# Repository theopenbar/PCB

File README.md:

# PCB-1
I2C Controller Board based on MCP23008
## This readme clearly shows how to use make the project step by step in simple ways happy making :)

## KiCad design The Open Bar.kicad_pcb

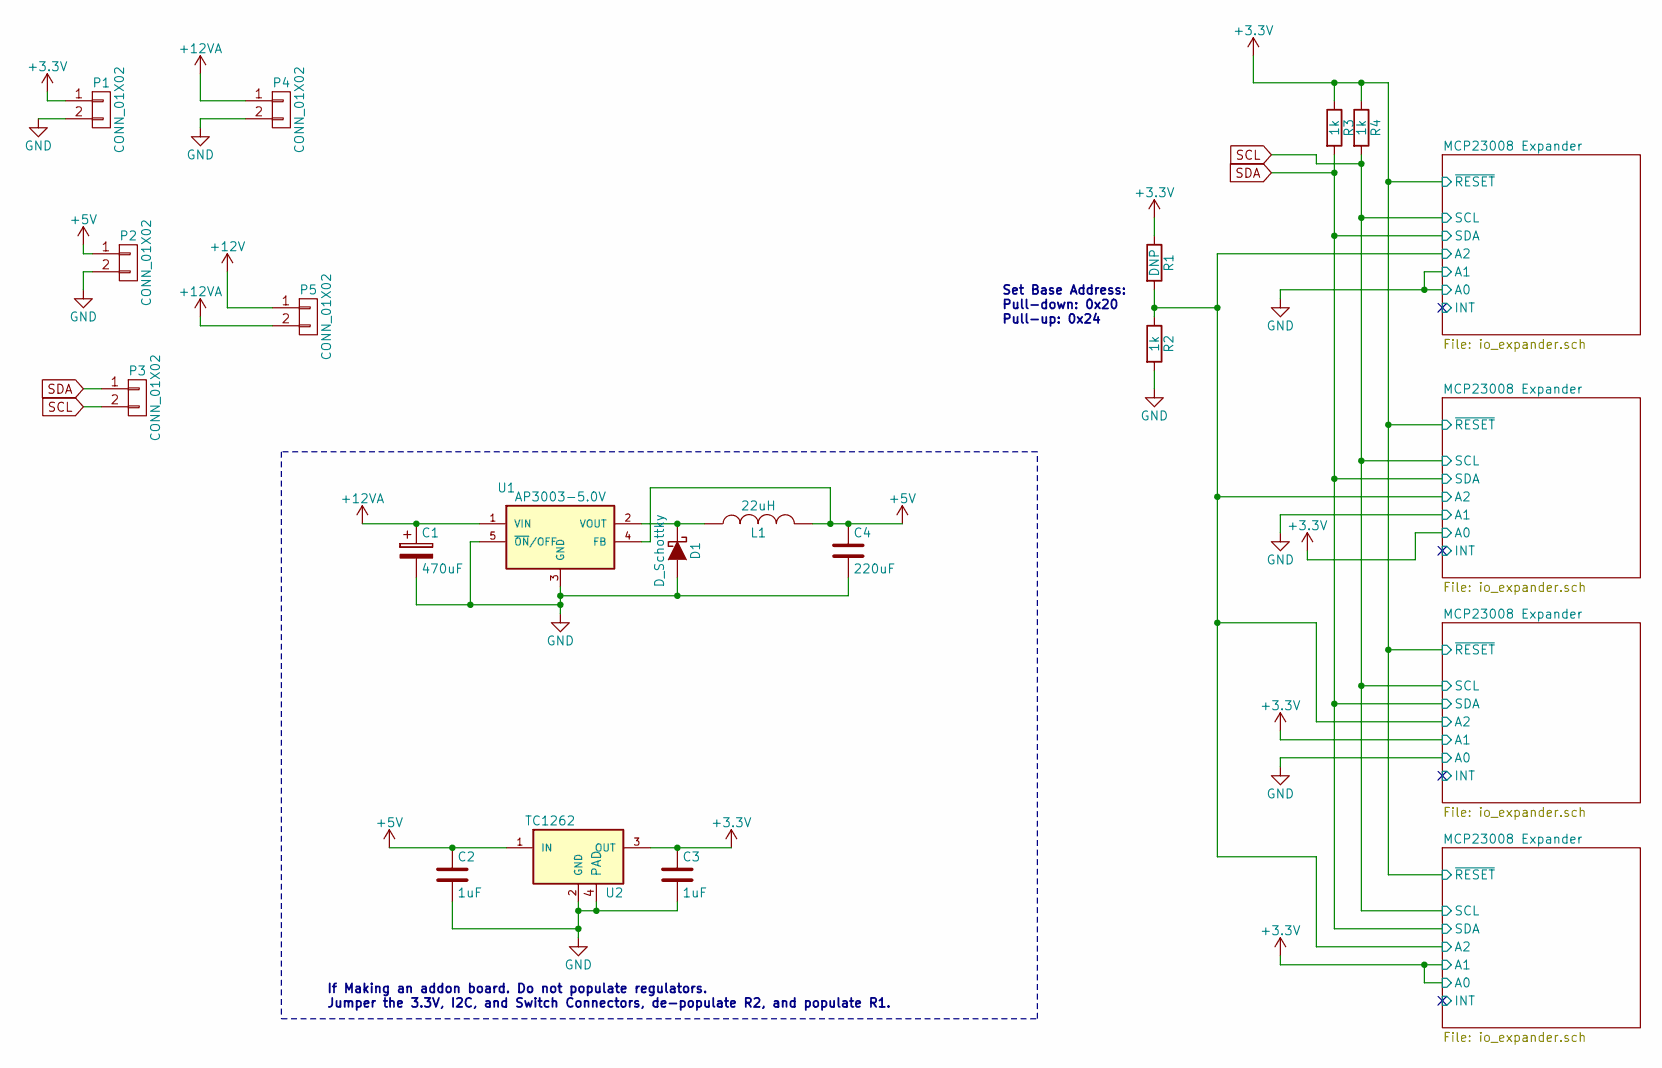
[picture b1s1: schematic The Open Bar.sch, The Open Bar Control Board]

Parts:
C1: 470uF; c_elec_10x10
C2, C3: 1uF; C_0402
C4: 220uF; C_1210
D1: D_Schottky; Diode_DO-201AD_Horizontal_RM15
L1: 22uH; SELF-WE-PD-XXL
P1, P2, P3, P4, P5: CONN_01X02; TerminalBlock_Pheonix_PT-3.5mm_2pol
R1: DNP; R_0402
R2, R3, R4: 1k; R_0402
U1: AP3003-5.0V; TO-263-5Lead
U2: TC1262; SOT-223

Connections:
+3V3: C3.1, P1.1, R1.1, R3.1, R4.1, U2.3 (OUT); also elsewhere on the board
+5V: C2.1, C4.1, L1.2, P2.1, U1.4 (FB), U2.1 (IN)
+12V: P5.1; also elsewhere on the board
+12VA: C1.1, P4.1, P5.2, U1.1 (VIN)
/MCP23008 Expander/A2: R1.2, R2.1; also elsewhere on the board
GND: C1.2, C2.2, C3.2, C4.2, D1.2 (A), P1.2, P2.2, P4.2, R2.2, U1.3 (GND), U1.5 (~ON~/OFF), U2.2 (GND), U2.4 (PAD); also elsewhere on the board
unnamed: D1.1 (K), L1.1, U1.2 (VOUT)
SCL: P3.2, R4.2; also elsewhere on the board
SDA: P3.1, R3.2; also elsewhere on the board

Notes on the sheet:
Set Base Address: Pull-down: 0x20 Pull-up: 0x24
If Making an addon board. Do not populate regulators. Jumper the 3.3V, I2C, and Switch Connectors, de-populate R2, and populate R1.

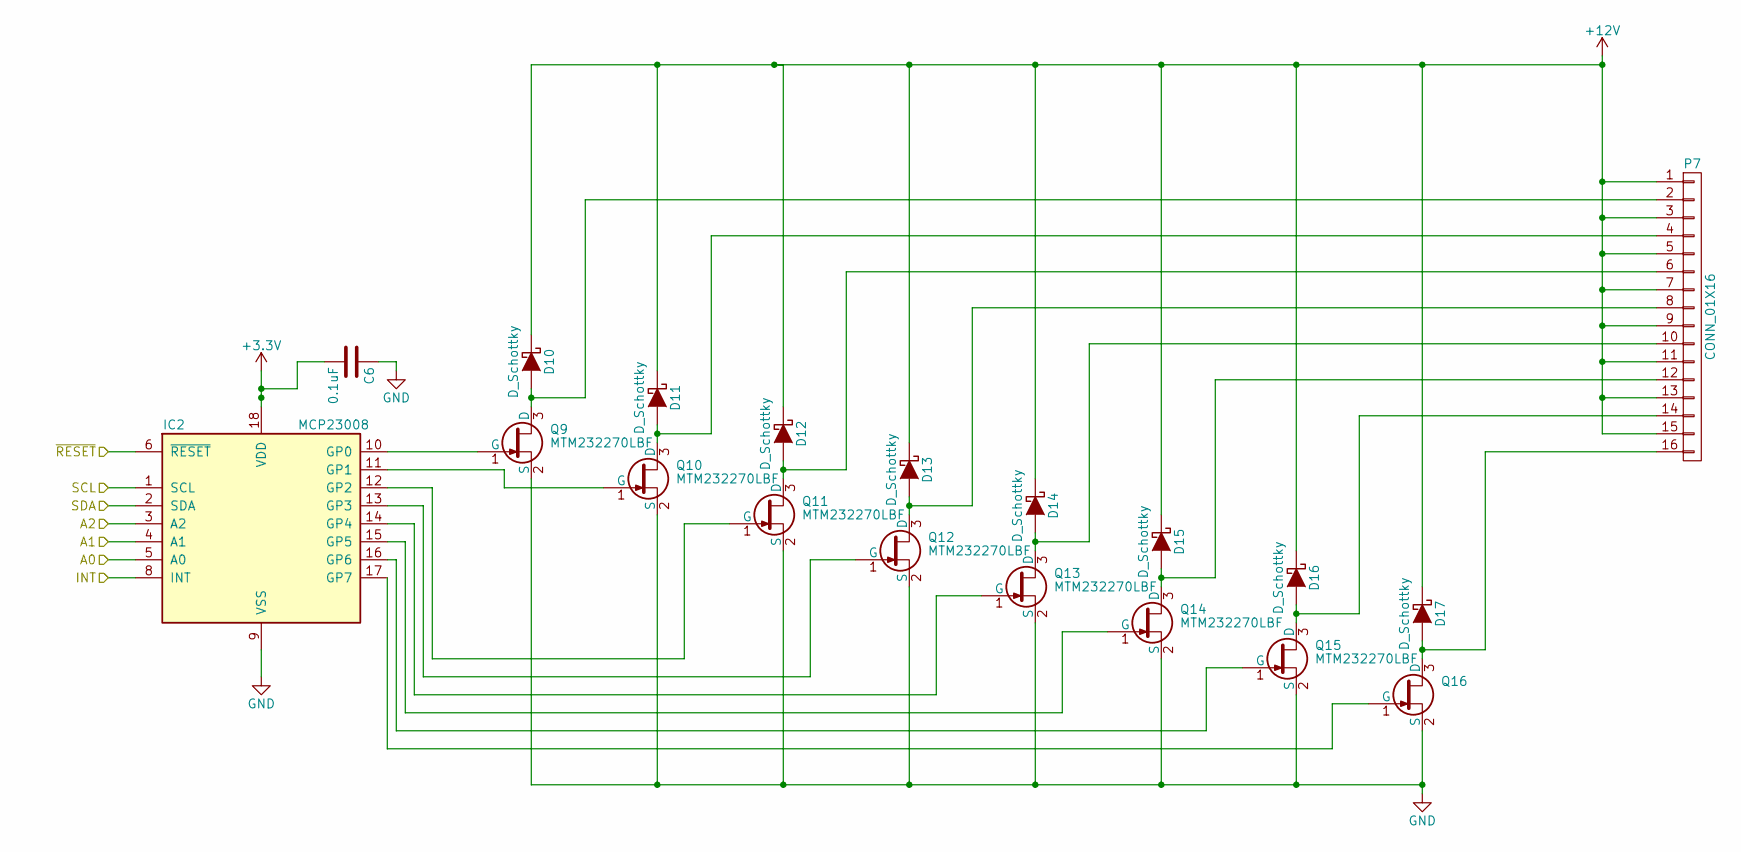
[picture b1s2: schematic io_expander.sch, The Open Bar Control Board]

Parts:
C5: 0.1uF; C_0402
D2, D3, D4, D5, D6, D7, D8, D17: D_Schottky; microSMP
IC1: MCP23008; SOIC-18_7.5x11.6mm_Pitch1.27mm
P6: CONN_01X16; TerminalBlock_Pheonix_PT-3.5mm_16pol
Q1, Q2, Q3, Q4, Q5, Q6, Q7, Q8: MTM232270LBF; SC-70

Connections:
+3V3: C5.2, IC1.6 (~RESET), IC1.18 (VDD); also elsewhere on the board
+12V: D2.1 (K), D3.1 (K), D4.1 (K), D5.1 (K), D6.1 (K), D7.1 (K), D8.1 (K), D17.1 (K), P6.1, P6.3, P6.5, P6.7, P6.9, P6.11, P6.13, P6.15; also elsewhere on the board
/MCP23008 Expander/A2: IC1.3 (A2); also elsewhere on the board
/MCP23008 Expander/INT: IC1.8 (INT); also elsewhere on the board
GND: C5.1, IC1.4 (A1), IC1.5 (A0), IC1.9 (VSS), Q1.2 (S), Q2.2 (S), Q3.2 (S), Q4.2 (S), Q5.2 (S), Q6.2 (S), Q7.2 (S), Q8.2 (S); also elsewhere on the board
unnamed: D2.2 (A), P6.2, Q1.3 (D)
unnamed: D3.2 (A), P6.4, Q2.3 (D)
unnamed: D4.2 (A), P6.6, Q3.3 (D)
unnamed: D5.2 (A), P6.8, Q4.3 (D)
unnamed: D6.2 (A), P6.10, Q5.3 (D)
unnamed: D7.2 (A), P6.12, Q6.3 (D)
unnamed: D8.2 (A), P6.14, Q7.3 (D)
unnamed: IC1.10 (GP0), Q1.1 (G)
unnamed: IC1.11 (GP1), Q2.1 (G)
unnamed: IC1.12 (GP2), Q3.1 (G)
unnamed: IC1.13 (GP3), Q4.1 (G)
unnamed: IC1.14 (GP4), Q5.1 (G)
unnamed: IC1.15 (GP5), Q6.1 (G)
unnamed: IC1.16 (GP6), Q7.1 (G)
unnamed: IC1.17 (GP7), Q8.1 (G)
SCL: IC1.1 (SCL); also elsewhere on the board
SDA: IC1.2 (SDA); also elsewhere on the board

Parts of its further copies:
C6, C7, C8: 0.1uF; C_0402
D9, D10, D11, D12, D13, D14, D15, D16, D18, D19, D20, D21, D22, D23, D24, D25, D26, D27, D28, D29, D30, D31, D32, D33: D_Schottky; microSMP
IC2, IC3, IC4: MCP23008; SOIC-18_7.5x11.6mm_Pitch1.27mm
P7, P8, P9: CONN_01X16; TerminalBlock_Pheonix_PT-3.5mm_16pol
Q9, Q10, Q11, Q12, Q13, Q14, Q15, Q16, Q17, Q18, Q19, Q20, Q21, Q22, Q23, Q24, Q25, Q26, Q27, Q28, Q29, Q30, Q31, Q32: MTM232270LBF; SC-70

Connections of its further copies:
+3V3: C6.2, C7.2, C8.2, IC2.5 (A0), IC2.6 (~RESET), IC2.18 (VDD), IC3.4 (A1), IC3.6 (~RESET), IC3.18 (VDD), IC4.4 (A1), IC4.5 (A0), IC4.6 (~RESET), IC4.18 (VDD); also elsewhere on the board
+12V: D9.1 (K), D10.1 (K), D11.1 (K), D12.1 (K), D13.1 (K), D14.1 (K), D15.1 (K), D16.1 (K), D18.1 (K), D19.1 (K), D20.1 (K), D21.1 (K), D22.1 (K), D23.1 (K), D24.1 (K), D25.1 (K), D26.1 (K), D27.1 (K), D28.1 (K), D29.1 (K), D30.1 (K), D31.1 (K), D32.1 (K), D33.1 (K), P7.1, P7.3, P7.5, P7.7, P7.9, P7.11, P7.13, P7.15, P8.1, P8.3, P8.5, P8.7, P8.9, P8.11, P8.13, P8.15, P9.1, P9.3, P9.5, P9.7, P9.9, P9.11, P9.13, P9.15; also elsewhere on the board
/MCP23008 Expander/A2: IC2.3 (A2), IC3.3 (A2), IC4.3 (A2); also elsewhere on the board
/MCP23008 Expander/INT: IC2.8 (INT), IC3.8 (INT), IC4.8 (INT); also elsewhere on the board
GND: C6.1, C7.1, C8.1, IC2.4 (A1), IC2.9 (VSS), IC3.5 (A0), IC3.9 (VSS), IC4.9 (VSS), Q9.2 (S), Q10.2 (S), Q11.2 (S), Q12.2 (S), Q13.2 (S), Q14.2 (S), Q15.2 (S), Q16.2 (S), Q17.2 (S), Q18.2 (S), Q19.2 (S), Q20.2 (S), Q21.2 (S), Q22.2 (S), Q23.2 (S), Q24.2 (S), Q25.2 (S), Q26.2 (S), Q27.2 (S), Q28.2 (S), Q29.2 (S), Q30.2 (S), Q31.2 (S), Q32.2 (S); also elsewhere on the board
unnamed: D10.2 (A), P7.2, Q9.3 (D)
unnamed: D11.2 (A), P7.4, Q10.3 (D)
unnamed: D12.2 (A), P7.6, Q11.3 (D)
unnamed: D13.2 (A), P7.8, Q12.3 (D)
unnamed: D14.2 (A), P7.10, Q13.3 (D)
unnamed: D15.2 (A), P7.12, Q14.3 (D)
unnamed: D16.2 (A), P7.14, Q15.3 (D)
unnamed: D18.2 (A), P8.2, Q17.3 (D)
unnamed: D19.2 (A), P8.4, Q18.3 (D)
unnamed: D20.2 (A), P8.6, Q19.3 (D)
unnamed: D21.2 (A), P8.8, Q20.3 (D)
unnamed: D22.2 (A), P8.10, Q21.3 (D)
unnamed: D23.2 (A), P8.12, Q22.3 (D)
unnamed: D24.2 (A), P8.14, Q23.3 (D)
unnamed: D25.2 (A), P8.16, Q24.3 (D)
unnamed: D26.2 (A), P9.2, Q25.3 (D)
unnamed: D27.2 (A), P9.4, Q26.3 (D)
unnamed: D28.2 (A), P9.6, Q27.3 (D)
unnamed: D29.2 (A), P9.8, Q28.3 (D)
unnamed: D30.2 (A), P9.10, Q29.3 (D)
unnamed: D31.2 (A), P9.12, Q30.3 (D)
unnamed: D32.2 (A), P9.14, Q31.3 (D)
unnamed: D33.2 (A), P9.16, Q32.3 (D)
unnamed: IC2.10 (GP0), Q9.1 (G)
unnamed: IC2.11 (GP1), Q10.1 (G)
unnamed: IC2.12 (GP2), Q11.1 (G)
unnamed: IC2.13 (GP3), Q12.1 (G)
unnamed: IC2.14 (GP4), Q13.1 (G)
unnamed: IC2.15 (GP5), Q14.1 (G)
unnamed: IC2.16 (GP6), Q15.1 (G)
unnamed: IC2.17 (GP7), Q16.1 (G)
unnamed: IC3.10 (GP0), Q17.1 (G)
unnamed: IC3.11 (GP1), Q18.1 (G)
unnamed: IC3.12 (GP2), Q19.1 (G)
unnamed: IC3.13 (GP3), Q20.1 (G)
unnamed: IC3.14 (GP4), Q21.1 (G)
unnamed: IC3.15 (GP5), Q22.1 (G)
unnamed: IC3.16 (GP6), Q23.1 (G)
unnamed: IC3.17 (GP7), Q24.1 (G)
unnamed: IC4.10 (GP0), Q25.1 (G)
unnamed: IC4.11 (GP1), Q26.1 (G)
unnamed: IC4.12 (GP2), Q27.1 (G)
unnamed: IC4.13 (GP3), Q28.1 (G)
unnamed: IC4.14 (GP4), Q29.1 (G)
unnamed: IC4.15 (GP5), Q30.1 (G)
unnamed: IC4.16 (GP6), Q31.1 (G)
unnamed: IC4.17 (GP7), Q32.1 (G)
SCL: IC2.1 (SCL), IC3.1 (SCL), IC4.1 (SCL); also elsewhere on the board
SDA: IC2.2 (SDA), IC3.2 (SDA), IC4.2 (SDA); also elsewhere on the board

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
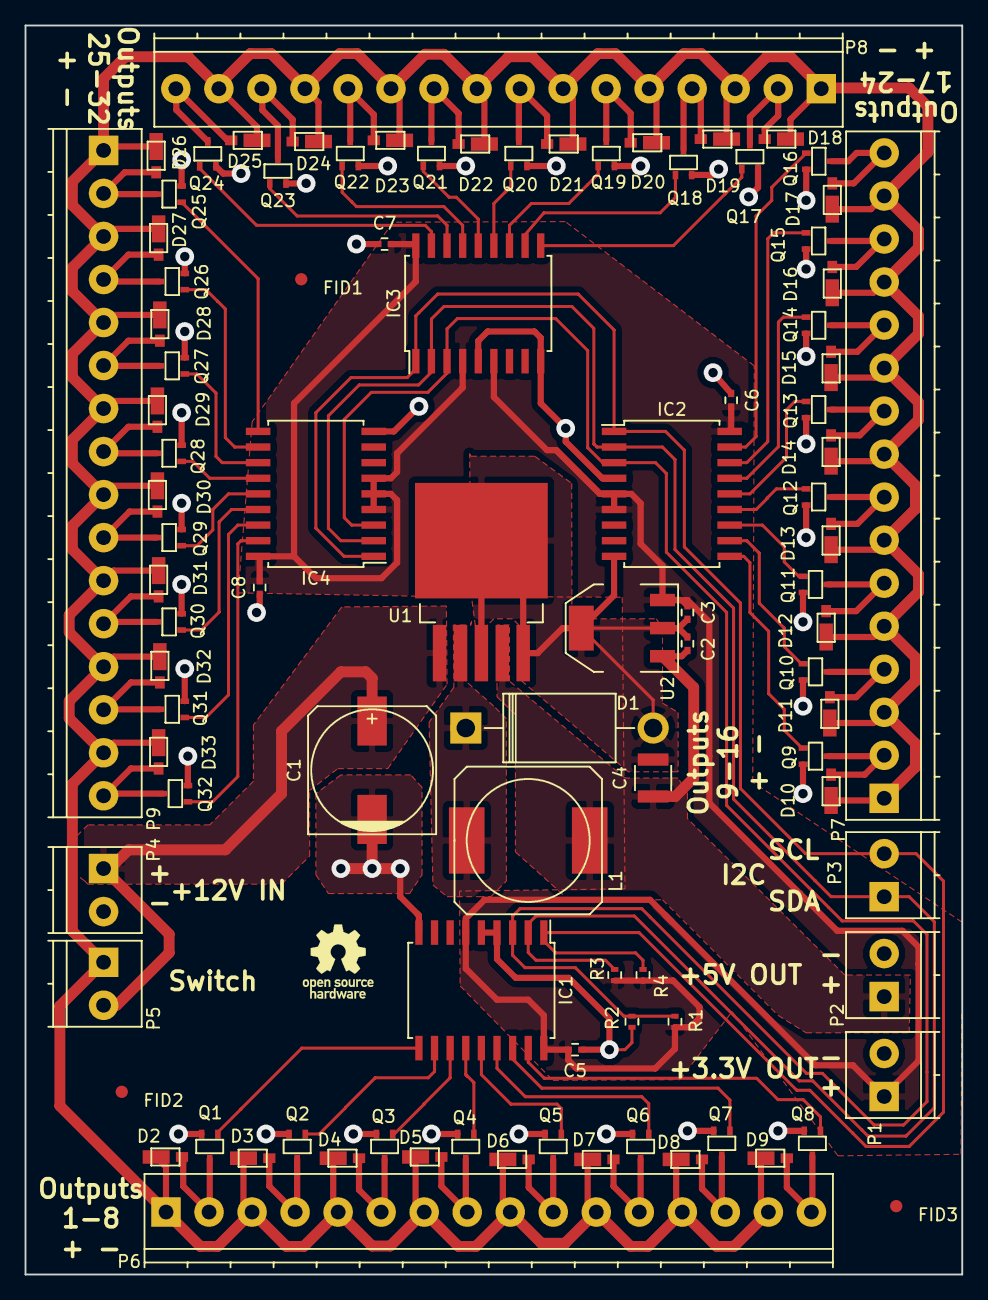
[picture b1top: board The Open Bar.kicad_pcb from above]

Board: 2 copper layers, 76.2 x 101.6 mm, 96 parts (0 on the bottom side), 74 nets.

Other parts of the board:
FID1, FID2, FID3: Fiducial_Modern_CopperTop; Fiducial_1mm_Dia_2.54mm_Outer_CopperTop

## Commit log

2016-08-04 Initial Commit Rev A
2016-08-04 Apply License
2016-08-04 Fix License Formatting
2017-02-25 Rev B, Added Flywheel Diodes
2017-02-25 Add BOM
2017-02-25 Update BOM
2017-02-27 Remove extra .drl file
2017-03-21 Added Fiducials and Fixed Diode Orientation
2017-04-12 Fix Unconnected Mosfet on PCB
